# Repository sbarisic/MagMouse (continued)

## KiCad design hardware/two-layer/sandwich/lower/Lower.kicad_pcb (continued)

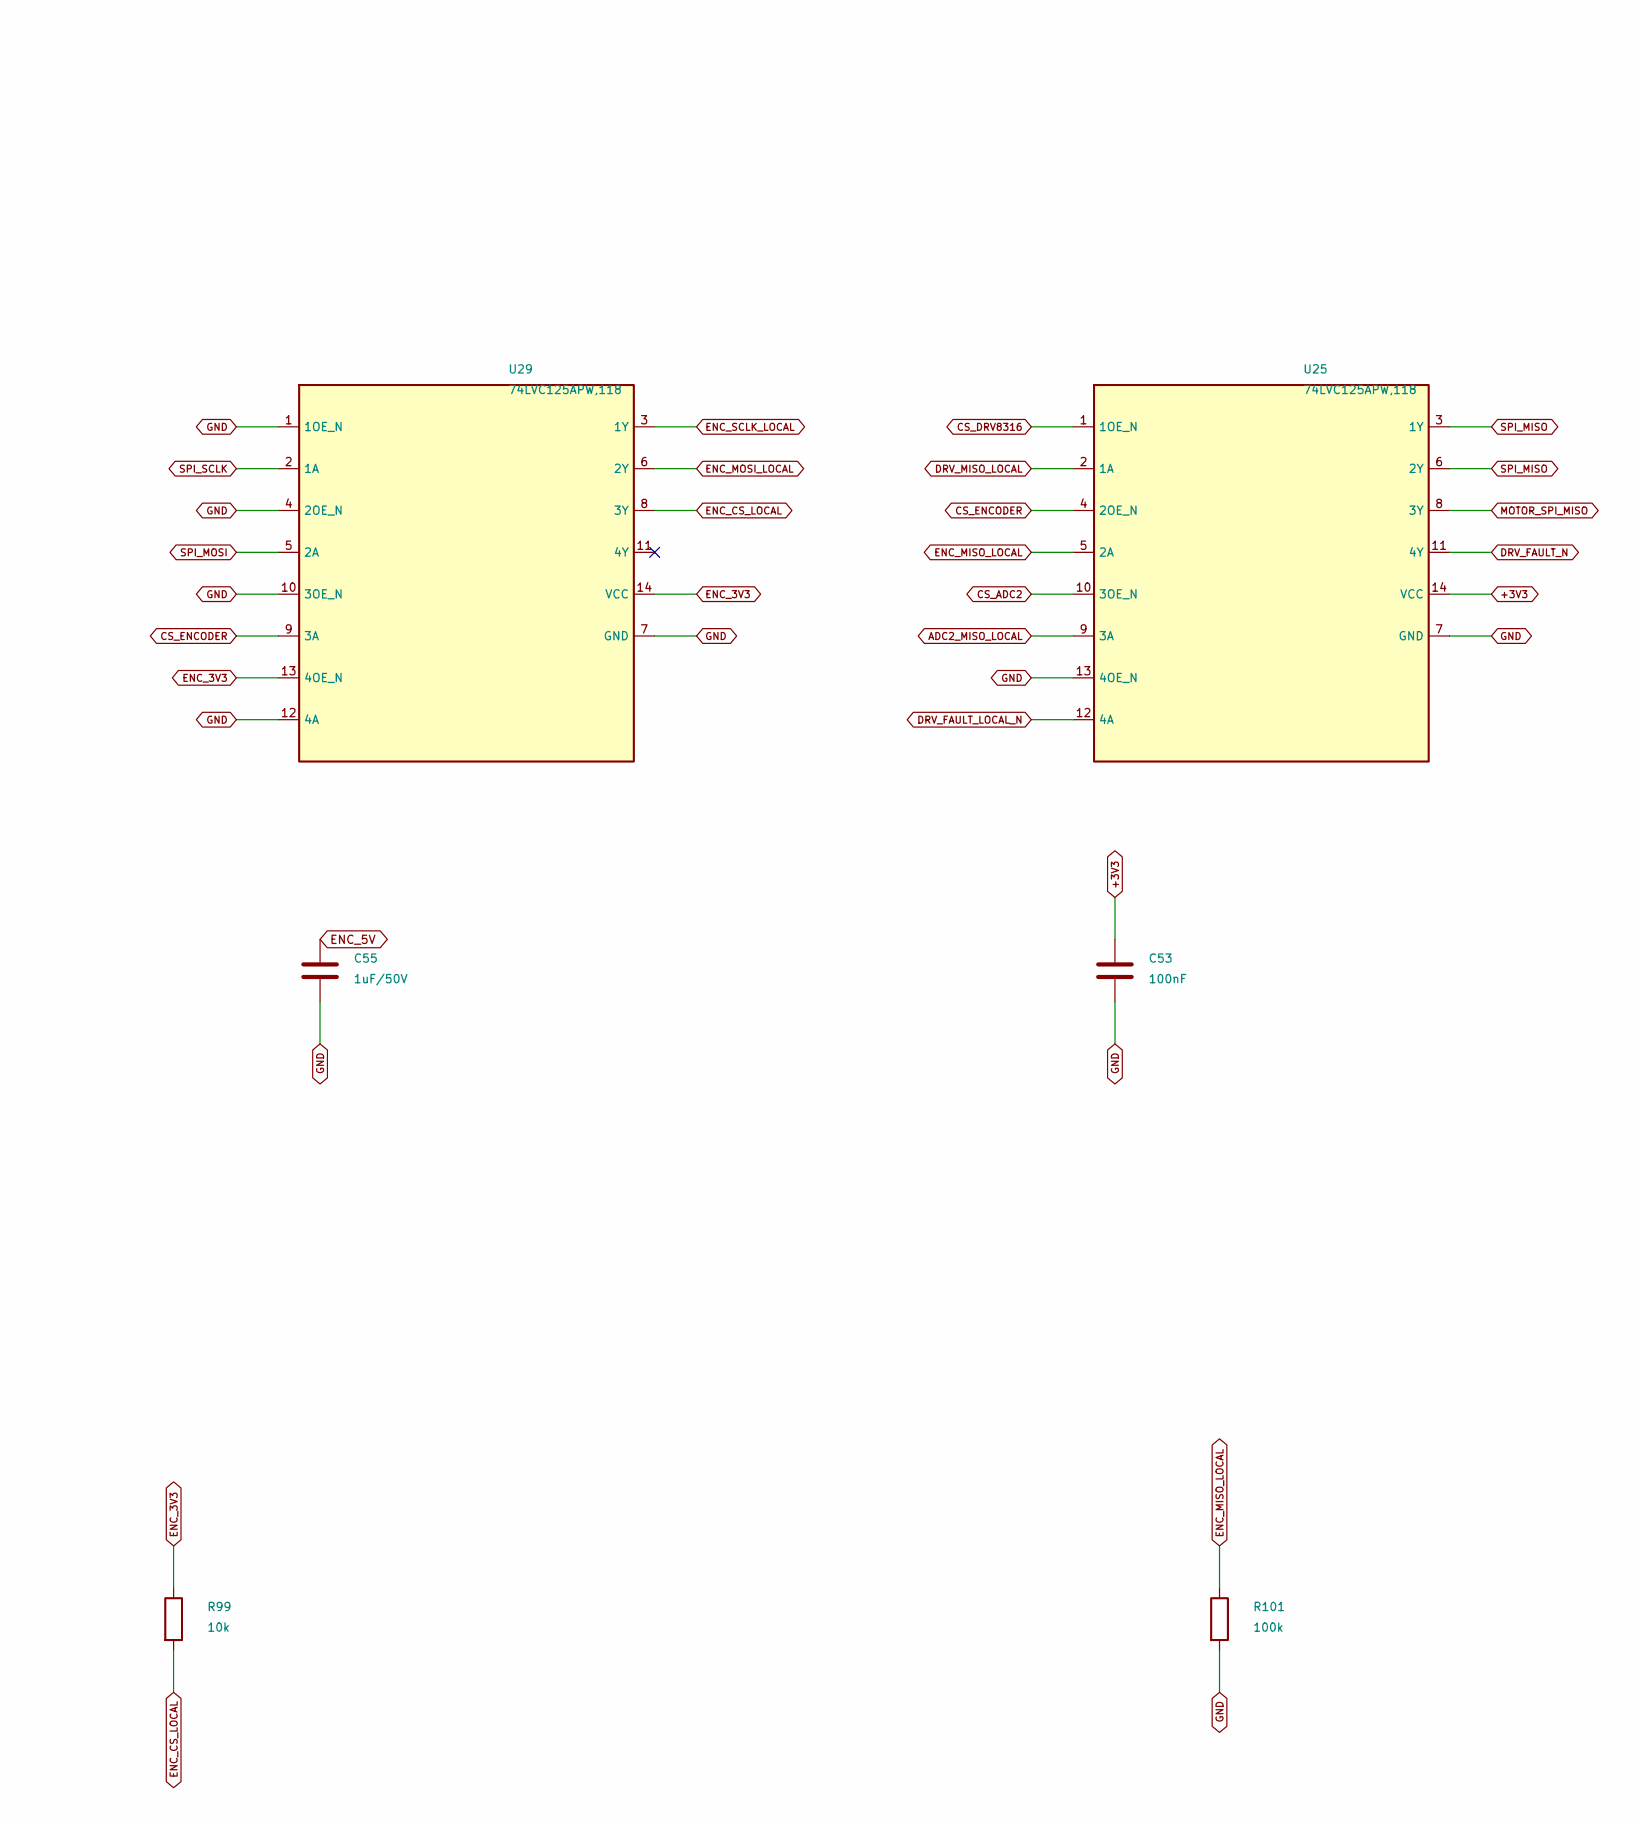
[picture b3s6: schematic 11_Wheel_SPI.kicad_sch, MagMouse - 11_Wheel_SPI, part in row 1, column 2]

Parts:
C53: 100nF; C_1206_3216Metric; Rating 50 V, X7R, 10%; MPN CC1206KRX7R9BB104
C55: 1uF/50V; C_1206_3216Metric; Rating 50 V, X7R, 10%; MPN CL31B105KBHNNNE
R99: 10k; R_1206_3216Metric; Rating 0.25 W, 1%; MPN RC1206FR-0710KL
R101: 100k; R_1206_3216Metric; Rating 0.25 W, 1%; MPN RC1206FR-07100KL
U25, U29: 74LVC125APW,118; TSSOP-14_4.4x5mm_P0.65mm; MPN 74LVC125APW,118; LCSC C6059

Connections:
+3V3: C53.1, U25.14 (VCC); also elsewhere on the board
ADC2_MISO_LOCAL: U25.9 (3A); also elsewhere on the board
CS_ADC2: U25.10 (3OE_N); also elsewhere on the board
CS_DRV8316: U25.1 (1OE_N); also elsewhere on the board
CS_ENCODER: U25.4 (2OE_N), U29.9 (3A); also elsewhere on the board
DRV_FAULT_LOCAL_N: U25.12 (4A); also elsewhere on the board
DRV_FAULT_N: U25.11 (4Y); also elsewhere on the board
DRV_MISO_LOCAL: U25.2 (1A); also elsewhere on the board
ENC_3V3: R99.1, U29.13 (4OE_N), U29.14 (VCC); also elsewhere on the board
ENC_5V: C55.1; also elsewhere on the board
ENC_CS_LOCAL: R99.2, U29.8 (3Y); also elsewhere on the board
ENC_MISO_LOCAL: R101.1, U25.5 (2A); also elsewhere on the board
ENC_MOSI_LOCAL: U29.6 (2Y); also elsewhere on the board
ENC_SCLK_LOCAL: U29.3 (1Y); also elsewhere on the board
GND: C53.2, C55.2, R101.2, U25.7 (GND), U25.13 (4OE_N), U29.1 (1OE_N), U29.4 (2OE_N), U29.7 (GND), U29.10 (3OE_N), U29.12 (4A); also elsewhere on the board
MOTOR_SPI_MISO: U25.8 (3Y); also elsewhere on the board
SPI_MISO: U25.3 (1Y), U25.6 (2Y); also elsewhere on the board
SPI_MOSI: U29.5 (2A); also elsewhere on the board
SPI_SCLK: U29.2 (1A); also elsewhere on the board

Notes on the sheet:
11_Wheel_SPI - Main owned components only See 18_Wheel_Harness for connector/bias additions; see INTERFACE_REVIEW.md for limits.

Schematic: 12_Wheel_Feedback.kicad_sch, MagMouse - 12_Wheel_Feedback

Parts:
C63, C64: 1uF/50V; C_1206_3216Metric; Rating 50 V, X7R, 10%; MPN CL31B105KBHNNNE
C105: 100nF/50V; C_1206_3216Metric; Rating 50 V, X7R, 10%; MPN CC1206KRX7R9BB104
J6: GB1806 AS5048A encoder wires; Wire_Signal_2x04_P2.54mm
R110: 100k; R_1206_3216Metric; Rating 0.25 W, 1%; MPN RC1206FR-07100KL
R125: 0R; R_1206_3216Metric; Rating Jumper, 2 A; MPN RC1206JR-070RL
U28: TPS22919DCKR; SOT-363_SC-70-6; MPN TPS22919DCKR; LCSC C2149796
U42: TLV75533PDBVR; SOT-23-5; MPN TLV75533PDBVR

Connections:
ENC_3V3: C64.1, C105.1, U42.5 (OUT); also elsewhere on the board
ENC_5V: J6.1, R125.2, U28.6 (OUT), U42.1 (IN), U42.3 (EN); also elsewhere on the board
ENC_CS_LOCAL: J6.6; also elsewhere on the board
ENC_MISO_LOCAL: J6.8; also elsewhere on the board
ENC_MOSI_LOCAL: J6.5; also elsewhere on the board
ENC_QOD: R125.1, U28.5 (QOD)
ENC_SCLK_LOCAL: J6.3; also elsewhere on the board
GND: C63.2, C64.2, C105.2, J6.2, J6.4, J6.7, R110.2, U28.2 (GND), U42.2 (GND); also elsewhere on the board
HALL_EN: R110.1, U28.3 (ON); also elsewhere on the board
RGB_5V: C63.1, U28.1 (IN); also elsewhere on the board

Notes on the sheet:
12_Wheel_Feedback - Main owned components only See 18_Wheel_Harness for connector/bias additions; see INTERFACE_REVIEW.md for limits.

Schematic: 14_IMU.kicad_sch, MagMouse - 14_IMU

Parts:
C70: 100nF; C_1206_3216Metric; Rating 50 V, X7R, 10%; MPN CC1206KRX7R9BB104
C71: 2.2uF/10V; C_1206_3216Metric; Rating 25 V, X7R, 10%; MPN CL31B225KAHNNNE
C72: 10nF; C_1206_3216Metric_OneSideSilk; Rating 50 V, X7R, 10%; MPN CC1206KRX7R9BB103
R126, R127: 10k; R_1206_3216Metric; Rating 0.25 W, 1%; MPN RC1206FR-0710KL
U32: ICM-42688-P; LGA-14_3x2.5mm_P0.5mm_LayoutBorder3x4y; MPN ICM-42688-P; LCSC C1850418

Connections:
+3V3: C70.1, C71.1, C72.1, R127.1, U32.5 (VDDIO), U32.8 (VDD); also elsewhere on the board
CS_IMU: U32.12 (AP_CS); also elsewhere on the board
GND: C70.2, C71.2, C72.2, R126.2, U32.6 (GND), U32.7 (RESV_GND); also elsewhere on the board
IMU_INT1: R127.2, U32.4 (INT1); also elsewhere on the board
IMU_PIN9: R126.1, U32.9 (INT2_FSYNC_CLKIN)
SPI_MISO: U32.1 (AP_SDO); also elsewhere on the board
SPI_MOSI: U32.14 (AP_SDI); also elsewhere on the board
SPI_SCLK: U32.13 (AP_SCLK); also elsewhere on the board

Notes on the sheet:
14 / Inertial sensing on shared SPI2
DRAFT 0.6 - CIRCUIT DEVELOPMENT ONLY - NOT FOR FABRICATION
C70/C71: place at VDD pin 8. C72: place at VDDIO pin 5. Both supplies remain on system +3V3. SPI2 mode 0, initial target 10MHz; CS setup/hold and MISO release guard >=100ns. R73 on sheet 09 holds CS high at boot. Internal clock; INT1 active-low open-drain with R127 pull-up. Pin 7 must be grounded. 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
Pin 9 has a 10k pulldown to avoid shorting a configurable output; select FSYNC input and leave FSYNC disabled. Wait >=1ms after valid power before register access; read WHO_AM_I=0x47 and configure interface/interrupts. Keep IMU in sleep for USB suspend. Prove shared-bus operation and vibration reje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

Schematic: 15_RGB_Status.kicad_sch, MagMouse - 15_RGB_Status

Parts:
C73, C74: 10uF/25V; C_1206_3216Metric; Rating 25 V, X5R, 10%; MPN CL31A106KAHNNNE
C75, C76: 100nF; C_1206_3216Metric; Rating 50 V, X7R, 10%; MPN CC1206KRX7R9BB104
D5: SK6805-EC15; OPSCO_SK6805_EC15; MPN SK6805-EC15; LCSC C2890035
R128: 330R; R_1206_3216Metric; Rating 0.25 W, 1%; MPN RC1206FR-07330RL
R129: 100k; R_1206_3216Metric; Rating 0.25 W, 1%; MPN RC1206FR-07100KL
R130: 10k; R_1206_3216Metric; Rating 0.25 W, 1%; MPN RC1206FR-0710KL
TP38: RGB_5V; TestPoint_Pad_D1.0mm
TP39: RGB_DIN; TestPoint_Pad_D1.0mm
U33: TPS7A2450DBVR; SOT-23-5; MPN TPS7A2450DBVR; LCSC C2864436
U34: SN74LV1T34DBVR; SOT-23-5; MPN SN74LV1T34DBVR; LCSC C100024

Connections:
GND: C73.2, C74.2, C75.2, C76.2, D5.4 (GND), R129.2, R130.2, U33.2 (GND), U34.3 (GND); also elsewhere on the board
HALL_EN: U33.3 (EN); also elsewhere on the board
PWR_5V: C73.1, U33.1 (IN); also elsewhere on the board
RGB_5V: C74.1, C75.1, C76.1, D5.2 (VDD), R130.1, TP38.1, U33.5 (OUT), U34.5 (VCC); also elsewhere on the board
RGB_BUFFER_OUT: R128.1, U34.4 (Y)
RGB_DATA: U34.2 (A); also elsewhere on the board
RGB_DIN: D5.1 (DIN), R128.2, R129.1, TP39.1

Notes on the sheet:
15 / Single-data-pin status LED with switched protected supply
DRAFT 0.6 - CIRCUIT DEVELOPMENT ONLY - NOT FOR FABRICATION
U33 caps the LED rail near 5V; in dropout RGB_5V follows PWR_5V minus dropout. This is not a boost supply. HALL_EN low disables RGB with Hall/encoder sleep; R130 discharges local storage. ACT_5V is never used. U34 shifts 3.3V data to the LED rail. R78 on sheet 09 preserves GPIO45 boot-low; no LED-r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
Firmware: hold data low during rail transitions; send black before suspend, then lower HALL_EN. Target 800kbps GRB/MSB-first; A1 timing 0=0.30/0.95us, 1=0.90/0.35us, reset low >=300us. Qualify startup/dropout, discharge, bus current and RGB_DIN timing on hardware. LED supply must stay 3.7..5.5V.

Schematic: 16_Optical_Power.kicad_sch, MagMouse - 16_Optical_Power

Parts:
C77, C78: 10uF/25V; C_1206_3216Metric; Rating 25 V, X5R, 10%; MPN CL31A106KAHNNNE
C79: 1nF/50V; C_1206_3216Metric; Rating 50 V, X7R, 10%; MPN CC1206KRX7R9BB102
C81, C82: 2.2uF/10V; C_1206_3216Metric; Rating 25 V, X7R, 10%; MPN CL31B225KAHNNNE
C83, C85: 100nF; C_1206_3216Metric; Rating 50 V, X7R, 10%; MPN CC1206KRX7R9BB104
C84: 4.7uF/10V; C_1206_3216Metric; Rating 25 V, X5R, 10%; MPN CL31A475KAHNNNE
R132: 39R; R_1206_3216Metric; Rating 0.25 W, 1%; MPN RC1206FR-0739RL
U36: TLV75519PDBVR; SOT-23-5; MPN TLV75519PDBVR; LCSC C2865381
U38: TPS22918DBVR; SOT-23-6; MPN TPS22918DBVR; LCSC C131941

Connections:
+3V3: C77.1, C78.1, U38.1 (VIN); also elsewhere on the board
GND: C77.2, C78.2, C79.2, C81.2, C82.2, C83.2, C84.2, C85.2, U36.2 (GND), U38.2 (GND); also elsewhere on the board
HALL_EN: U38.3 (ON); also elsewhere on the board
OPT_1V9: C82.1, C83.1, R132.1, U36.5 (OUT); also elsewhere on the board
OPT_3V3: C81.1, U36.1 (IN), U36.3 (EN), U38.6 (VOUT); also elsewhere on the board
OPT_LED_P: R132.2; also elsewhere on the board
OPT_RAMP_CT: C79.1, U38.4 (CT)
OPT_VDDPIX: C84.1, C85.1; also elsewhere on the board

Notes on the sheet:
16_Optical_Power - Main owned components only See 18_Wheel_Harness for connector/bias additions; see INTERFACE_REVIEW.md for limits.

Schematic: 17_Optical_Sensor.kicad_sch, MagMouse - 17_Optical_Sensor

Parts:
C80, C86, C87: 100nF; C_1206_3216Metric; Rating 50 V, X7R, 10%; MPN CC1206KRX7R9BB104
R131, R135: 10k; R_1206_3216Metric; Rating 0.25 W, 1%; MPN RC1206FR-0710KL
R133, R134, R136: 100k; R_1206_3216Metric; Rating 0.25 W, 1%; MPN RC1206FR-07100KL
U35: PMW3360DM-T2QU; PixArt_PMW3360DM_T2QU; MPN PMW3360DM-T2QU; LCSC C20612443
U37: 74LVC125APW,118; TSSOP-14_4.4x5mm_P0.65mm; MPN 74LVC125APW,118; LCSC C6059
U39: SN74LVC1G125DBVR; SOT-23-5; MPN SN74LVC1G125DBVR; LCSC C23654

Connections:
CS_PAW: U37.1 (1OE_N), U37.4 (2OE_N), U37.10 (3OE_N), U39.2 (A); also elsewhere on the board
GND: C80.2, C86.2, C87.2, R134.2, U35.8 (GND), U37.7 (GND), U37.13 (4OE_N), U39.1 (OE_N), U39.3 (GND); also elsewhere on the board
OPT_1V9: U35.4 (VDD_1V9); also elsewhere on the board
OPT_3V3: C80.1, C86.1, C87.1, R131.1, R133.1, R135.1, R136.1, U35.5 (VDDIO), U37.14 (VCC), U39.5 (VCC); also elsewhere on the board
OPT_CS_N: R131.2, U35.13 (NCS), U39.4 (Y)
OPT_CTRL: U37.12 (4A); also elsewhere on the board
OPT_LED_P: U35.15 (LED_P); also elsewhere on the board
OPT_MISO: R135.2, U35.12 (MISO), U37.9 (3A)
OPT_MOSI: R134.1, U35.11 (MOSI), U37.3 (1Y)
OPT_RESET_N: U35.7 (NRESET), U37.11 (4Y)
OPT_SCLK: R133.2, U35.10 (SCLK), U37.6 (2Y)
OPT_VDDPIX: U35.3 (VDDPIX_OUT); also elsewhere on the board
PAW_MOTION_N: R136.2, U35.9 (MOTION); also elsewhere on the board
SPI_MISO: U37.8 (3Y); also elsewhere on the board
SPI_MOSI: U37.2 (1A); also elsewhere on the board
SPI_SCLK: U37.5 (2A); also elsewhere on the board

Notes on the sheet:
17 / PMW3360 with selected-device SPI isolation and buffered reset
DRAFT 0.7 - CIRCUIT DEVELOPMENT ONLY - NOT FOR FABRICATION
SPI2 mode 3, <=2MHz. Set SCLK high before selecting; CS setup/read hold/release guard >=1us. U37 disconnects sensor clock, MOSI and MISO while CS_PAW is high; reset channel is always enabled. R72 holds CS high and R79 holds OPT_CTRL low at boot. Keep all CS high during reset and rail transitions. S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
OPT_CTRL low asserts reset despite the internal pull-up (600uA max). U39 isolates CS when unpowered. After valid rails: reset, wait >=50ms, clear motion registers, load authorized SROM and verify identity. Suspend: send Shutdown, deselect, assert reset, clear SENS_REQ. Resume requires full initiali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

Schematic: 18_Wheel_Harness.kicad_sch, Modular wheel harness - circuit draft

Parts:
J8: Wheel 17-wire signals / 2 GND; Wire_Wheel_17_P2.54mm
R141, R142, R143: 33k; R_1206_3216Metric; Rating 0.25 W, 1%; MPN RC1206FR-0733KL

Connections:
+3V3: J8.16; also elsewhere on the board
ACT_DRIVE_EN: J8.13; also elsewhere on the board
ADC2_MISO_LOCAL: J8.9, R143.1; also elsewhere on the board
CS_ADC2: J8.8; also elsewhere on the board
CS_DRV8316: J8.4; also elsewhere on the board
DRV_FAULT_LOCAL_N: J8.15, R141.1; also elsewhere on the board
DRV_MISO_LOCAL: J8.5, R142.1; also elsewhere on the board
GND: J8.1, J8.17, R141.2, R142.2, R143.2; also elsewhere on the board
MOTOR_SPI_MOSI: J8.7; also elsewhere on the board
MOTOR_SPI_SCLK: J8.6; also elsewhere on the board
SPI_MOSI: J8.3; also elsewhere on the board
SPI_SCLK: J8.2; also elsewhere on the board
WHEEL_PWM_A: J8.10; also elsewhere on the board
WHEEL_PWM_B: J8.11; also elsewhere on the board
WHEEL_PWM_C: J8.12; also elsewhere on the board
WHEEL_RUN_REQ: J8.14; also elsewhere on the board

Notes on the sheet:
18_Wheel_Harness / Lower components See 20_Stack_Harness for the inter-board wiring.

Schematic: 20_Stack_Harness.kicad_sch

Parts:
H101, H102, H103, H104: M2 clearance / 5mm support envelope; MountingHole_2.2mm_M2_5mm_Envelope
J101: Stack signals / 14 wires; Wire_Stack_Signal_14
J103: Stack power / 5 wires; Wire_Stack_Power_5

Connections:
+3V3: J103.4; also elsewhere on the board
ACT_DRIVE_EN: J101.13; also elsewhere on the board
ACT_HEARTBEAT: J101.7; also elsewhere on the board
ACT_REQ: J101.6; also elsewhere on the board
ADC_CS: J101.5; also elsewhere on the board
CC_OUT1: J101.9; also elsewhere on the board
CC_OUT2: J101.10; also elsewhere on the board
GND: J101.1, J103.1, J103.5; also elsewhere on the board
HALL_EN: J101.12; also elsewhere on the board
MCU_EN: J101.14; also elsewhere on the board
PWR_5V: J103.3; also elsewhere on the board
SENS_REQ: J101.8; also elsewhere on the board
SPI_MISO: J101.4; also elsewhere on the board
SPI_MOSI: J101.3; also elsewhere on the board
SPI_SCLK: J101.2; also elsewhere on the board
VBUS_PRESENT_N: J101.11; also elsewhere on the board
VBUS_USB: J103.2; also elsewhere on the board

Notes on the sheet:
Connect equal-numbered signal and power pads between Lower and Upper. 19 wires total: 13 signals, 3 supply rails, 3 shared grounds. All three buttons use passive plastic clicks and Hall sensing.

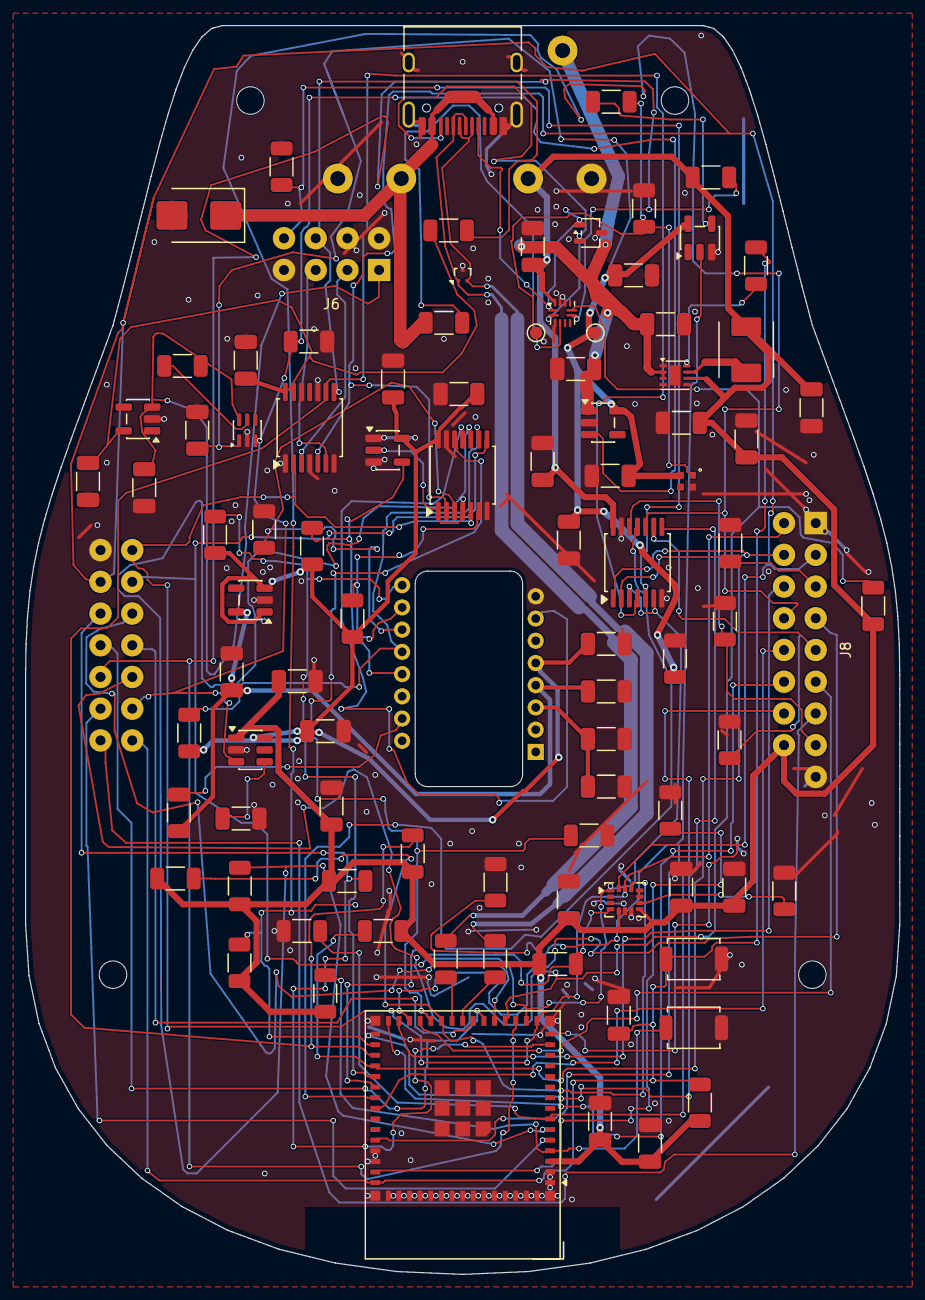
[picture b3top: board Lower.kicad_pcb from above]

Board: 2 copper layers, 70.0 x 100.0 mm, 100 parts (0 on the bottom side), 69 nets.

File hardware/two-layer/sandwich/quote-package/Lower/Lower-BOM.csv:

Comment,Designator,Footprint,LCSC Part #,Manufacturer,MPN,Quantity
10uF/25V,"C1,C2,C23,C3,C5,C73,C74,C77,C78",C_1206_3216Metric,,Samsung Electro-Mechanics,CL31A106KAHNNNE,9
100nF/50V,C105,C_1206_3216Metric,,YAGEO,CC1206KRX7R9BB104,1
100nF,"C22,C53,C6,C70,C75,C76,C80,C83,C85,C86,C87",C_1206_3216Metric,,YAGEO,CC1206KRX7R9BB104,11
1uF/50V,"C4,C55,C63,C64",C_1206_3216Metric,,Samsung Electro-Mechanics,CL31B105KBHNNNE,4
2.2uF/10V,"C71,C81,C82",C_1206_3216Metric,,Samsung Electro-Mechanics,CL31B225KAHNNNE,3
10nF,C72,C_1206_3216Metric_OneSideSilk,,YAGEO,CC1206KRX7R9BB103,1
1nF/50V,C79,C_1206_3216Metric,,YAGEO,CC1206KRX7R9BB102,1
4.7uF/10V,C84,C_1206_3216Metric,,Samsung Electro-Mechanics,CL31A475KAHNNNE,1
SMBJ12A,D1,D_SMB,C151251,Littelfuse,SMBJ12A,1
SK6805-EC15,D5,OPSCO_SK6805_EC15,C2890035,OPSCO Optoelectronics,SK6805-EC15,1
TYPE-C-31-M-12,J1,USB_C_Receptacle_HRO_TYPE-C-31-M-12,C165948,Korean Hroparts Elec,TYPE-C-31-M-12,1
SRP4020CC-3R3M,L1,L_Bourns_SRP4020CC,,Bourns,SRP4020CC-3R3M,1
100k,"R101,R110,R129,R133,R134,R136,R26,R27",R_1206_3216Metric,,YAGEO,RC1206FR-07100KL,8
0R,R125,R_1206_3216Metric,,YAGEO,RC1206JR-070RL,1
10k,"R126,R127,R130,R131,R135,R3,R4,R7,R72,R73,R74,R75,R76,R77,R78,R79,R80,R99",R_1206_3216Metric,,YAGEO,RC1206FR-0710KL,18
330R,R128,R_1206_3216Metric,,YAGEO,RC1206FR-07330RL,1
39R,R132,R_1206_3216Metric,,YAGEO,RC1206FR-0739RL,1
33k,"R141,R142,R143",R_1206_3216Metric,,YAGEO,RC1206FR-0733KL,3
887k,R25,R_1206_3216Metric,,YAGEO,RC1206FR-07887KL,1
1k,R28,R_1206_3216Metric,,YAGEO,RC1206FR-071KL,1
33R,"R5,R6",R_1206_3216Metric,,YAGEO,RC1206FR-0733RL,2
RESET,SW1,SW_SPST_TS-1088-xR020,C720477,XUNPU,TS-1088-AR02016,1
BOOT,SW2,SW_SPST_TS-1088-xR020,C720477,XUNPU,TS-1088-AR02016,1
TPD2EUSB30DRTR,U1,Texas_DRT-3,C97502,Texas Instruments,TPD2EUSB30DRTR,1
TUSB320LAIRWBR,U11,Texas_X2QFN-12_1.6x1.6mm_P0.4mm,C132554,Texas Instruments,TUSB320LAIRWBR,1
TPS62162DSGR,U2,Texas_DSG0008A_WSON-8-1EP_2x2mm_P0.5mm_EP0.9x1.6mm,C40256,Texas Instruments,TPS62162DSGR,1
TPD2E2U06DCKR,U20,SOT-323_SC-70,C1855726,Texas Instruments,TPD2E2U06DCKR,1
"74LVC125APW,118","U25,U29,U37",TSSOP-14_4.4x5mm_P0.65mm,C6059,Nexperia,"74LVC125APW,118",3
TPS22919DCKR,U28,SOT-363_SC-70-6,C2149796,Texas Instruments,TPS22919DCKR,1
ESP32-S3-MINI-1-N8,U3,ESP32-S2-MINI-1,C2913206,Espressif Systems,ESP32-S3-MINI-1-N8,1
ICM-42688-P,U32,LGA-14_3x2.5mm_P0.5mm_LayoutBorder3x4y,C1850418,TDK InvenSense,ICM-42688-P,1
TPS7A2450DBVR,U33,SOT-23-5,C2864436,Texas Instruments,TPS7A2450DBVR,1
SN74LV1T34DBVR,U34,SOT-23-5,C100024,Texas Instruments,SN74LV1T34DBVR,1
PMW3360DM-T2QU,U35,PixArt_PMW3360DM_T2QU,C20612443,PixArt,PMW3360DM-T2QU,1
TLV75519PDBVR,U36,SOT-23-5,C2865381,Texas Instruments,TLV75519PDBVR,1
TPS22918DBVR,U38,SOT-23-6,C131941,Texas Instruments,TPS22918DBVR,1
SN74LVC1G125DBVR,U39,SOT-23-5,C23654,Texas Instruments,SN74LVC1G125DBVR,1
TLV75533PDBVR,U42,SOT-23-5,,Texas Instruments,TLV75533PDBVR,1

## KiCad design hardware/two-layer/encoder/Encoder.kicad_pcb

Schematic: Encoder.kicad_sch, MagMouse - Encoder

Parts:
C62: 1uF/50V; C_1206_3216Metric; Rating 50 V, X7R, 10%; MPN CL31B105KBHNNNE
J7: Soldered wires Signal_2x04; Wire_Signal_2x04_P2.54mm
U27: MA735GGU-P; MPS_UTQFN14_2x2; MPN MA735GGU-P; LCSC C17233427

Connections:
ENC_3V3: C62.1, J7.1, U27.13 (VDD)
ENC_CS_LOCAL: J7.6, U27.7 (CS)
ENC_MISO_LOCAL: J7.8, U27.5 (MISO)
ENC_MOSI_LOCAL: J7.5, U27.8 (MOSI)
ENC_SCLK_LOCAL: J7.3, U27.1 (SCLK)
GND: C62.2, J7.2, J7.4, J7.7, U27.2 (TEST), U27.4 (GND), U27.14 (SSCK)

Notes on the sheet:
Upright wheel encoder / MA735
DRAFT 0.1 - CIRCUIT DEVELOPMENT ONLY - NOT FOR FABRICATION
J7 mates to motherboard J6 using an eight-wire pin-to-pin harness. 3.3 V comes ONLY from the switched ENC_3V3 rail. Do not connect USB or 5 V.
Pin assignment (J6 = J7) 1 ENC_3V3 2 GND 3 SCLK 4 GND 5 MOSI 6 CS 7 GND 8 MISO Ground contacts are separate harness conductors. No live mating. Check continuity before power.
C62: local VDD bypass. TEST and SSCK grounded; other unused outputs NC. Start with the existing 64 us filter setting; validate angle age and 10 MHz cable operation. PCB outline/magnet gap/support geometry are provisional. The shell bracket carries mechanical loads.

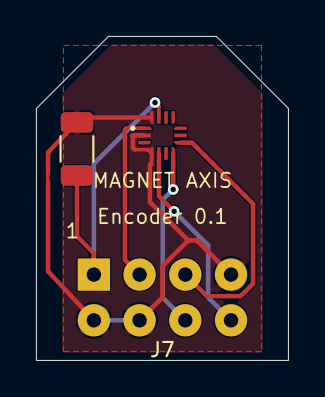
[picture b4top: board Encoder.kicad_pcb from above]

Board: 2 copper layers, 14.0 x 18.0 mm, 3 parts (0 on the bottom side), 6 nets.

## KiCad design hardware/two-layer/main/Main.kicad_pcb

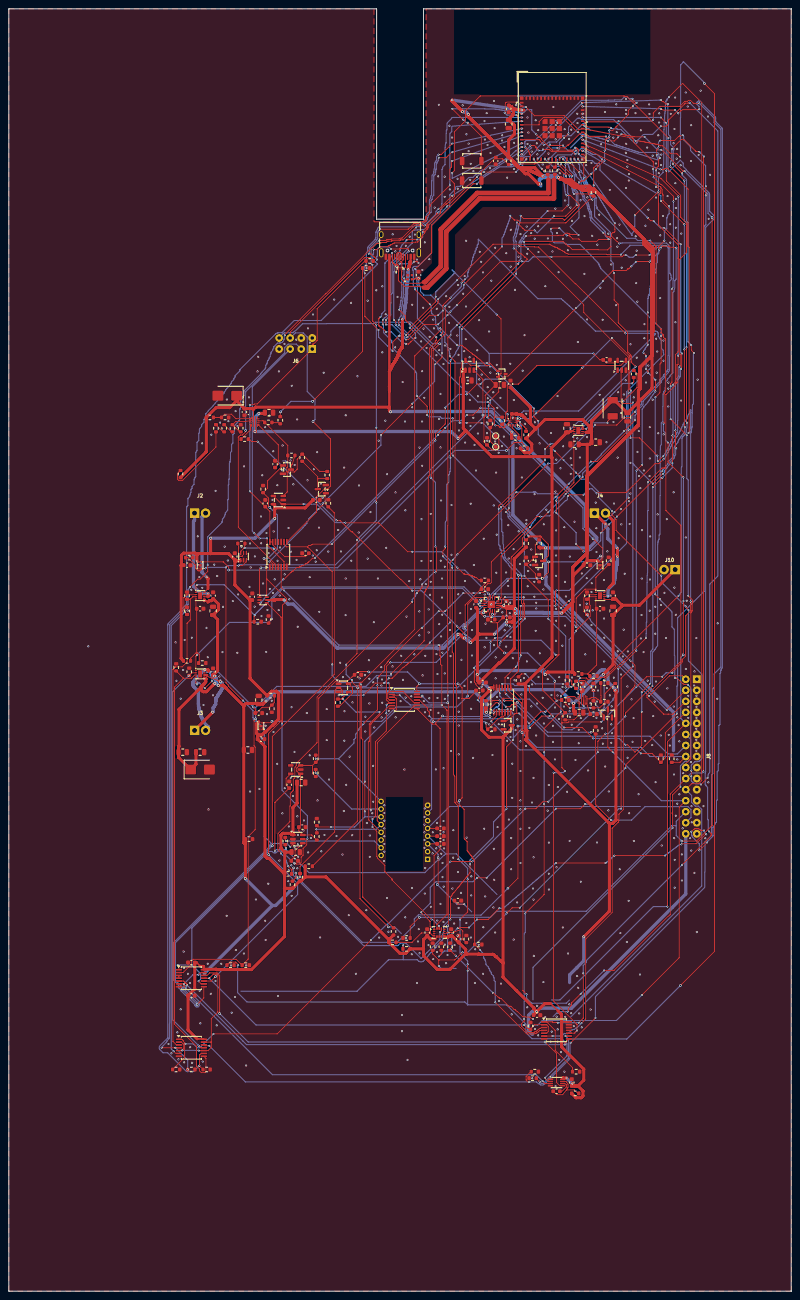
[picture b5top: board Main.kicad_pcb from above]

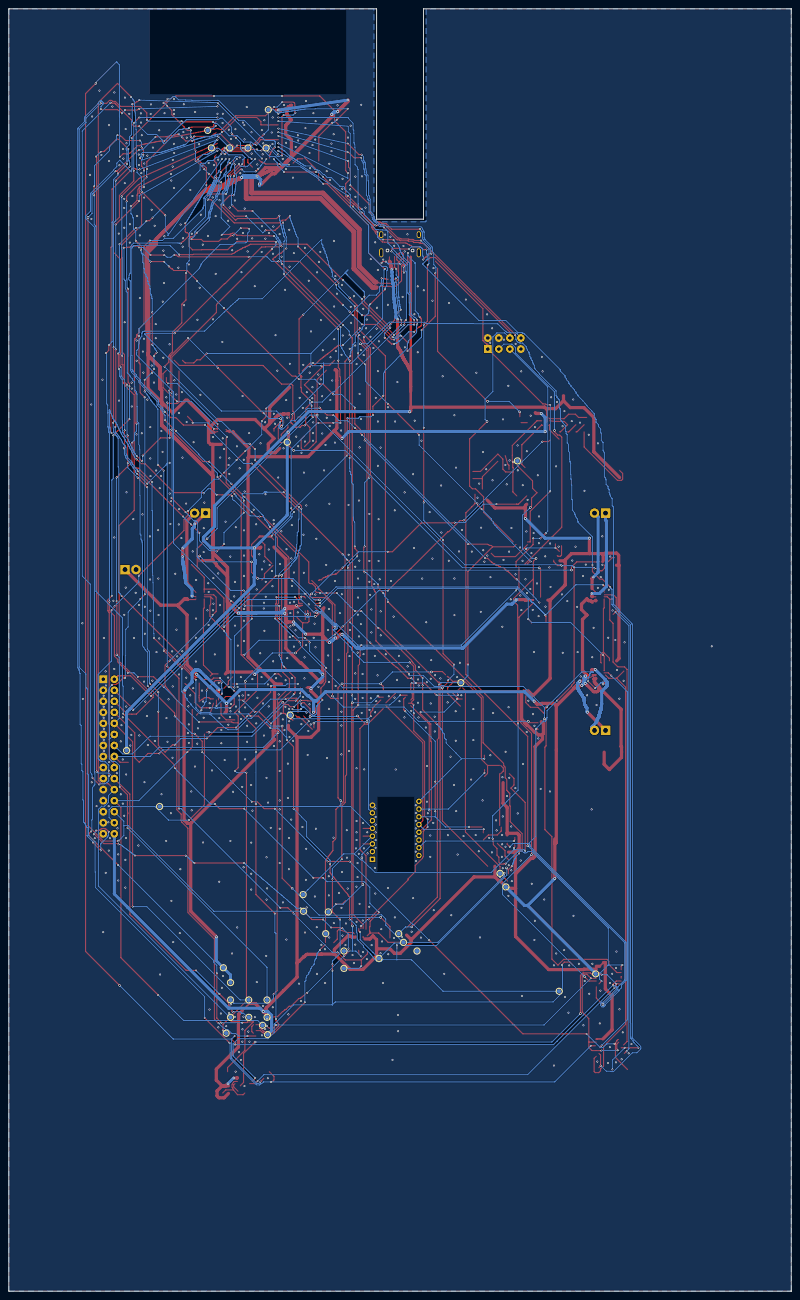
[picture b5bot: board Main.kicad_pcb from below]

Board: 2 copper layers, 180.0 x 295.0 mm, 246 parts (37 on the bottom side), 130 nets.

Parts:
C1, C2, C3, C5, C8, C11, C14, C23, C37, C38, C39, C40, C73, C74, C77, C78, C88: 10uF/25V; C_0805_2012Metric
C4, C19, C20, C21, C24, C27, C63, C89: 1uF/50V; C_0603_1608Metric
C6, C7, C9, C10, C12, C13, C15, C16, C17, C18, C22, C28, C29, C30, C31, C32, C33, C34, C35, C36, C53, C55, C64, C70, C75, C76, C80, C83, C85, C86, C87: 100nF; C_0603_1608Metric
C25, C26, C72: 10nF; C_0603_1608Metric
C71, C81, C82: 2.2uF/10V; C_0603_1608Metric
C79: 1nF/50V; C_0603_1608Metric
C84: 4.7uF/10V; C_0603_1608Metric
D1: SMBJ12A; D_SMB
D2: SMBJ6.0A; D_SMB
D3, D4: BAT54-7-F; SOT-23
D5: SK6805-EC15; OPSCO_SK6805_EC15
J1: TYPE-C-31-M-12; USB_C_Receptacle_HRO_TYPE-C-31-M-12
J2, J3, J4, J10: Soldered wires Power_1x02; Wire_Power_1x02_P2.54mm
J6: Soldered wires Signal_2x04; Wire_Signal_2x04_P2.54mm
J8: Soldered wires Signal_2x15; Wire_Signal_2x15_P2.54mm
L1: SRP4020CC-3R3M; L_Bourns_SRP4020CC
Q1, Q2, Q3: 2N7002; SOT-23
R3, R4, R7, R8, R9, R10, R11, R14, R15, R16, R17, R20, R21, R22, R23, R30, R46, R47, R48, R49, R50, R51, R52, R53, R54, R55, R61, R70, R72, R73, R74, R75, R76, R77, R78, R79, R80, R99, R126, R127, R130, R131, R135: 10k; R_0603_1608Metric
R5, R6, R58: 33R; R_0603_1608Metric
R12, R18, R24, R42, R43, R56, R57, R60: 3.3k; R_0603_1608Metric
R25: 887k; R_0603_1608Metric
R26, R27, R31, R32, R33, R34, R35, R36, R37, R38, R39, R40, R62, R63, R66, R67, R71, R101, R110, R129, R133, R134, R136: 100k; R_0603_1608Metric
R28, R44, R45, R64, R69: 1k; R_0603_1608Metric
R29, R41, R65, R68: 22.1k; R_0603_1608Metric
R59: 4.7k; R_0603_1608Metric
R125: 0R; R_0603_1608Metric
R128: 330R; R_0603_1608Metric
R132: 39R; R_0603_1608Metric
R141, R142, R143: 33k; R_0603_1608Metric
SW1: RESET; SW_SPST_TS-1088-xR020
SW2: BOOT; SW_SPST_TS-1088-xR020
TP1, TP10: VBUS_USB; TestPoint_Pad_D1.0mm
TP2, TP11: PWR_5V; TestPoint_Pad_D1.0mm
TP3, TP12: ACT_5V; TestPoint_Pad_D1.0mm
TP4: UART_TX; TestPoint_Pad_D1.0mm
TP5: UART_RX; TestPoint_Pad_D1.0mm
TP6: MCU_EN; TestPoint_Pad_D1.0mm
TP7: BOOT; TestPoint_Pad_D1.0mm
TP8: +3V3; TestPoint_Pad_D1.0mm
TP9, TP15: GND; TestPoint_Pad_D1.0mm
TP13: ACT_DRIVE_EN; TestPoint_Pad_D1.0mm
TP14: USB_ILM; TestPoint_Pad_D1.0mm
TP16: CS_PAW; TestPoint_Pad_D1.0mm
TP17: WHEEL_RUN_REQ; TestPoint_Pad_D1.0mm
TP18: CS_IMU; TestPoint_Pad_D1.0mm
TP19: OPT_CTRL; TestPoint_Pad_D1.0mm
TP20: MOTOR_SPI_MOSI; TestPoint_Pad_D1.0mm
TP21: MOTOR_SPI_SCLK; TestPoint_Pad_D1.0mm
TP22: MOTOR_SPI_MISO; TestPoint_Pad_D1.0mm
TP23: CS_ADC2; TestPoint_Pad_D1.0mm
TP24: CS_MA735; TestPoint_Pad_D1.0mm
TP25: CS_DRV8316; TestPoint_Pad_D1.0mm
TP26: PAW_MOTION_N; TestPoint_Pad_D1.0mm
TP27: IMU_INT1; TestPoint_Pad_D1.0mm
TP28: DRV_FAULT_N; TestPoint_Pad_D1.0mm
TP29: WHEEL_PWM_A; TestPoint_Pad_D1.0mm
TP30: RGB_DATA; TestPoint_Pad_D1.0mm
TP31: BOOT_SAFE_SPARE; TestPoint_Pad_D1.0mm
TP32: WHEEL_PWM_B; TestPoint_Pad_D1.0mm
TP33: WHEEL_PWM_C; TestPoint_Pad_D1.0mm
TP38: RGB_5V; TestPoint_Pad_D1.0mm
TP39: RGB_DIN; TestPoint_Pad_D1.0mm
TP40: OPT_3V3; TestPoint_Pad_D1.0mm
TP41: OPT_1V9; TestPoint_Pad_D1.0mm
TP42: OPT_VDDPIX; TestPoint_Pad_D1.0mm
TP43: OPT_RESET_N; TestPoint_Pad_D1.0mm
U1: TPD2EUSB30DRTR; Texas_DRT-3
U2: TPS62162DSGR; Texas_DSG0008A_WSON-8-1EP_2x2mm_P0.5mm_EP0.9x1.6mm
U3: ESP32-S3-MINI-1-N8; ESP32-S2-MINI-1
U4, U5, U6: DRV8231ADSGR; Texas_DSG0008A_WSON-8-1EP_2x2mm_P0.5mm_EP0.9x1.6mm
U7, U8, U9: TMAG5253BA2IQDMRR; Texas_X2SON-4-1EP_1.1x1.4mm_P0.5mm_EP0.8x0.6mm
U10: ADS7038IRTER; WQFN-16-1EP_3x3mm_P0.5mm_EP1.68x1.68mm
U11: TUSB320LAIRWBR; Texas_X2QFN-12_1.6x1.6mm_P0.4mm
U12, U13: TPS259470LRPWR; Texas_RPW0010A
U14: SN74LVC2G04DCKR; SOT-363_SC-70-6
U15: SN74LVC1G123DCUR; VSSOP-8_2.3x2mm_P0.5mm
U16, U17, U18: SN74LVC08APWR; TSSOP-14_4.4x5mm_P0.65mm
U19: TLV9001IDBVR; SOT-23-5
U20: TPD2E2U06DCKR; SOT-323_SC-70
U25, U29, U37: SN74LVC125APWR; TSSOP-14_4.4x5mm_P0.65mm
U28: TPS22919DCKR; SOT-363_SC-70-6
U32: ICM-42688-P; LGA-14_3x2.5mm_P0.5mm_LayoutBorder3x4y
U33: TPS7A2450DBVR; SOT-23-5
U34: SN74LV1T34DBVR; SOT-23-5
U35: PMW3360DM-T2QU; PixArt_PMW3360DM_T2QU
U36: TLV75519PDBVR; SOT-23-5
U38: TPS22918DBVR; SOT-23-6
U39: SN74LVC1G125DBVR; SOT-23-5

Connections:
+3V3: C2.1, C3.1, C5.1, C6.1, C16.1, C17.1, C18.1, C19.1, C20.1, C22.1, C23.1, C28.1, C29.1, C30.1, C31.1, C32.1, C34.1, C53.1, C63.1, C70.1, C71.1, C72.1, C77.1, C78.1, D4.3, J8.30, L1.2, R3.1, R4.1, R7.1, R10.1, R16.1, R22.1, R26.1, R27.1, R46.1, R71.1, R72.1, R73.1, R74.1, R75.1, R76.1, R127.1, TP8.1, U2.6, U3.3, U7.1, U8.1, U9.1, U10.7, U10.10, U11.12, U14.5, U15.8, U16.14, U17.14, U18.14, U19.5, U25.14, U28.1, U32.5, U32.8, U38.1
ACT_5V: C7.1, C8.1, C10.1, C11.1, C13.1, C14.1, C37.1, C38.1, C39.1, C40.1, D2.1, J10.1, R67.1, R69.1, TP3.1, TP12.1, U4.5, U5.5, U6.5, U13.6
ACT_DRIVE_EN: D3.3, J8.24, R49.1, TP13.1, U16.11, U17.2, U17.5, U17.10, U17.13, U18.2, U18.5
ACT_DVDT: C26.1, U13.7
ACT_FAULT_N: R45.1, U13.4
ACT_HEARTBEAT: R47.1, U3.21, U15.2
ACT_ILM: R42.1, R43.1, U13.9
ACT_OVLO: R40.2, R41.1, U13.2
ACT_PERMIT: U15.5, U16.12
ACT_REQ: R48.1, U3.20, U16.2
ACT_UVLO: D3.1, R38.2, R39.1, U13.1
ACT_UV_1: R36.2, R37.1
ACT_UV_2: R37.2, R38.1
ACT_VMON: C36.1, D4.1, R67.2, R68.1, U10.6
ADC2_MISO_LOCAL: J8.16, R143.1, U25.9
ADC_CS: R7.2, U3.14, U10.11
ADC_DECAP: C21.1, U10.8
ARM_SOURCE: U16.3, U16.4
ARM_VALID: U15.3, U16.6, U16.13
BOOT: R4.2, SW2.1, TP7.1, U3.4
BOOT_SAFE_SPARE: R80.1, TP31.1, U3.44
BTN_L_CMD1: R50.1, U3.8, U17.1
BTN_L_CMD2: R51.1, U3.9, U17.4
BTN_L_COIL_N: J2.2, U4.8
BTN_L_COIL_P: J2.1, U4.6
BTN_L_IN1: R8.1, U4.3, U17.3
BTN_L_IN2: R9.1, U4.2, U17.6
BTN_L_ISENSE: R12.1, U4.1, U10.2
BTN_L_VREF: C9.1, R10.2, R11.1, U4.4
BTN_M_CMD1: R52.1, U3.10, U17.9
BTN_M_CMD2: R53.1, U3.11, U17.12
BTN_M_COIL_N: J3.2, U5.8
BTN_M_COIL_P: J3.1, U5.6
BTN_M_IN1: R14.1, U5.3, U17.8
BTN_M_IN2: R15.1, U5.2, U17.11
BTN_M_ISENSE: R18.1, U5.1, U10.3
BTN_M_VREF: C12.1, R16.2, R17.1, U5.4
BTN_R_CMD1: R54.1, U3.12, U18.1
BTN_R_CMD2: R55.1, U3.13, U18.4
BTN_R_COIL_N: J4.2, U6.8
BTN_R_COIL_P: J4.1, U6.6
BTN_R_IN1: R20.1, U6.3, U18.3
BTN_R_IN2: R21.1, U6.2, U18.6
BTN_R_ISENSE: R24.1, U6.1, U10.4
BTN_R_VREF: C15.1, R22.2, R23.1, U6.4
BUCK_SW: L1.1, U2.7
CC_OUT1: R26.2, U3.18, U11.7, U14.1
CC_OUT2: R27.2, U3.19, U11.8, U14.3
CC_OUT2_INV: U14.4, U16.10
CC_VBUS_DET: R25.2, U11.4
CS_ADC2: J8.14, R74.2, TP23.1, U3.32, U25.10
CS_DRV8316: J8.6, R76.2, TP25.1, U3.34, U25.1
CS_IMU: R73.2, TP18.1, U3.25, U32.12
CS_MA735: R75.2, TP24.1, U3.33, U25.4, U29.9
CS_PAW: R72.2, TP16.1, U3.6, U37.1, U37.4, U37.10, U39.2
DRV_FAULT_LOCAL_N: J8.28, R141.1, U25.12
DRV_FAULT_N: TP28.1, U3.37, U25.11
DRV_MISO_LOCAL: J8.8, R142.1, U25.2
ENC_3V3: C55.1, C64.1, J6.1, R99.1, R125.2, U28.6, U29.13, U29.14
ENC_CS_LOCAL: J6.6, R99.2, U29.8
ENC_MISO_LOCAL: J6.8, R101.1, U25.5
ENC_MOSI_LOCAL: J6.5, U29.6
ENC_QOD: R125.1, U28.5
ENC_SCLK_LOCAL: J6.3, U29.3
GND: C1.2, C2.2, C3.2, C4.2, C5.2, C6.2, C7.2, C8.2, C9.2, C10.2, C11.2, C12.2, C13.2, C14.2, C15.2, C16.2, C17.2, C18.2, C19.2, C20.2, C21.2, C22.2, C23.2, C24.2, C25.2, C26.2, C28.2, C29.2, C30.2, C31.2, C32.2, C33.2, C34.2, C35.2, C36.2, C37.2, C38.2, C39.2, C40.2, C53.2, C55.2, C63.2, C64.2, C70.2, C71.2, C72.2, C73.2, C74.2, C75.2, C76.2, C77.2, C78.2, C79.2, C80.2, C81.2, C82.2, C83.2, C84.2, C85.2, C86.2, C87.2, C88.2, C89.2, D1.2, D2.2, D5.4, J1.A1, J1.A12, J1.B1, J1.B12, J1.SH, J6.2, J6.4, J6.7, J8.1, J8.3, J8.5, J8.7, J8.9, J8.11, J8.13, J8.15, J8.17, J8.19, J8.21, J8.23, J8.25, J8.27, J8.29, J10.2, Q1.2, Q2.2, Q3.2, R8.2, R9.2, R11.2, R12.2, R14.2, R15.2, R17.2, R18.2, R20.2, R21.2, R23.2, R24.2, R30.2, R35.2, R39.2, R41.2, R42.2, R43.2, R47.2, R48.2, R49.2, R50.2, R51.2, R52.2, R53.2, R54.2, R55.2, R58.2, R62.2, R63.2, R66.2, R68.2, R69.2, R70.2, R77.2, R78.2, R79.2, R80.2, R101.2, R110.2, R126.2, R129.2, R130.2, R134.2, R141.2, R142.2, R143.2, SW1.2, SW2.2, TP9.1, TP15.1, U1.3, U2.1, U2.4, U2.5, U2.9, U3.1, U3.2, U3.42, U3.43, U3.46, U3.47, U3.48, U3.49, U3.50, U3.51, U3.52, U3.53, U3.54, U3.55, U3.56, U3.57, U3.58, U3.59, U3.60, U3.61, U3.62, U3.63, U3.64, U3.65, U4.7, U4.9, U5.7, U5.9, U6.7, U6.9, U7.2, U7.5, U8.2, U8.5, U9.2, U9.5, U10.9, U10.17, U11.3, U11.10, U11.11, U12.8, U13.8, U14.2, U15.1, U15.4, U16.7, U17.7, U18.7, U18.12, U18.13, U19.2, U20.3, U25.7, U25.13, U28.2, U29.1, U29.4, U29.7, U29.10, U29.12, U32.6, U32.7, U33.2, U34.3, U35.8, U36.2, U37.7, U37.13, U38.2, U39.1, U39.3
HALL_EN: R110.1, U7.3, U8.3, U9.3, U16.5, U18.8, U28.3, U33.3, U38.3
HALL_L: U7.4, U10.15
HALL_M: U8.4, U10.16
HALL_R: U9.4, U10.1
ILM_BASE_1: R56.2, R57.1
ILM_BASE_2: R57.2, R58.1
ILM_HIGH_D: Q2.3, R60.2, R61.2
ILM_MED_D: Q1.3, R59.2
IMU_INT1: R127.2, TP27.1, U3.36, U32.4
IMU_PIN9: R126.1, U32.9
LOGIC_PG: R28.1, U2.8
MCU_EN: C4.1, R3.2, R28.2, R44.2, R45.2, SW1.1, TP6.1, U3.45, U18.10
MCU_USB_DM: R5.1, U3.23
MCU_USB_DP: R6.1, U3.24
MOTOR_SPI_MISO: TP22.1, U3.31, U25.8
MOTOR_SPI_MOSI: J8.12, TP20.1, U3.28
MOTOR_SPI_SCLK: J8.10, TP21.1, U3.29
OPT_1V9: C82.1, C83.1, R132.1, TP41.1, U35.4, U36.5
OPT_3V3: C80.1, C81.1, C86.1, C87.1, R131.1, R133.1, R135.1, R136.1, TP40.1, U35.5, U36.1, U36.3, U37.14, U38.6, U39.5
OPT_CS_N: R131.2, U35.13, U39.4
OPT_CTRL: R79.1, TP19.1, U3.26, U37.12
OPT_LED_P: R132.2, U35.15
OPT_MISO: R135.2, U35.12, U37.9
OPT_MOSI: R134.1, U35.11, U37.3
OPT_RAMP_CT: C79.1, U38.4
OPT_RESET_N: TP43.1, U35.7, U37.11
OPT_SCLK: R133.2, U35.10, U37.6
OPT_VDDPIX: C84.1, C85.1, TP42.1, U35.3
PAW_MOTION_N: R136.2, TP26.1, U3.35, U35.9
PWR_5V: C1.1, C73.1, C88.1, C89.1, R36.1, R40.1, TP2.1, TP11.1, U2.2, U2.3, U12.6, U13.5, U33.1
RGB_5V: C74.1, C75.1, C76.1, D5.2, R130.1, TP38.1, U33.5, U34.5
RGB_BUFFER_OUT: R128.1, U34.4
RGB_DATA: R78.1, TP30.1, U3.41, U34.2
RGB_DIN: D5.1, R128.2, R129.1, TP39.1
SENS_REQ: R70.1, U3.22, U18.9
SOURCE_3A: Q2.1, R63.1, U16.8
SOURCE_OK: Q1.1, R62.1, U14.6, U16.1, U16.9
SPI_MISO: U3.17, U10.12, U25.3, U25.6, U32.1, U37.8
SPI_MOSI: J8.4, U3.15, U10.14, U29.5, U32.14, U37.2
SPI_SCLK: J8.2, U3.16, U10.13, U29.2, U32.13, U37.5
UART_RX: TP5.1, U3.40
UART_TX: TP4.1, U3.39
USB_CC1: J1.A5, U11.1, U20.1
USB_CC2: J1.B5, U11.2, U20.2
USB_DM: J1.A7, J1.B7, R5.2, U1.2
USB_DP: J1.A6, J1.B6, R6.2, U1.1
USB_DVDT: C25.1, U12.7
USB_FAULT_N: R44.1, U12.4
USB_ILM: R56.1, R59.1, R60.1, R61.1, TP14.1, U12.9, U19.3
USB_IMON_ADC: C33.1, R64.2, U10.5
USB_IMON_BUF: R64.1, U19.1, U19.4
USB_OVLO: R34.2, R35.1, U12.2
USB_OV_1: R31.2, R32.1
USB_OV_2: R32.2, R33.1
USB_OV_3: R33.2, R34.1
USB_UVLO: R29.2, R30.1, U12.1
VBUS_GATE: C35.1, Q3.1, R65.2, R66.1
VBUS_PRESENT_N: Q3.3, R71.2, U3.5
VBUS_USB: C24.1, D1.1, J1.A4, J1.A9, J1.B4, J1.B9, R25.1, R29.1, R31.1, R65.1, TP1.1, TP10.1, U12.5
WD_CEXT: C27.2, U15.6
WD_RCEXT: C27.1, R46.2, U15.7
WHEEL_PWM_A: J8.18, TP29.1, U3.38
WHEEL_PWM_B: J8.20, TP32.1, U3.27
WHEEL_PWM_C: J8.22, TP33.1, U3.30
WHEEL_RUN_REQ: J8.26, R77.1, TP17.1, U3.7
